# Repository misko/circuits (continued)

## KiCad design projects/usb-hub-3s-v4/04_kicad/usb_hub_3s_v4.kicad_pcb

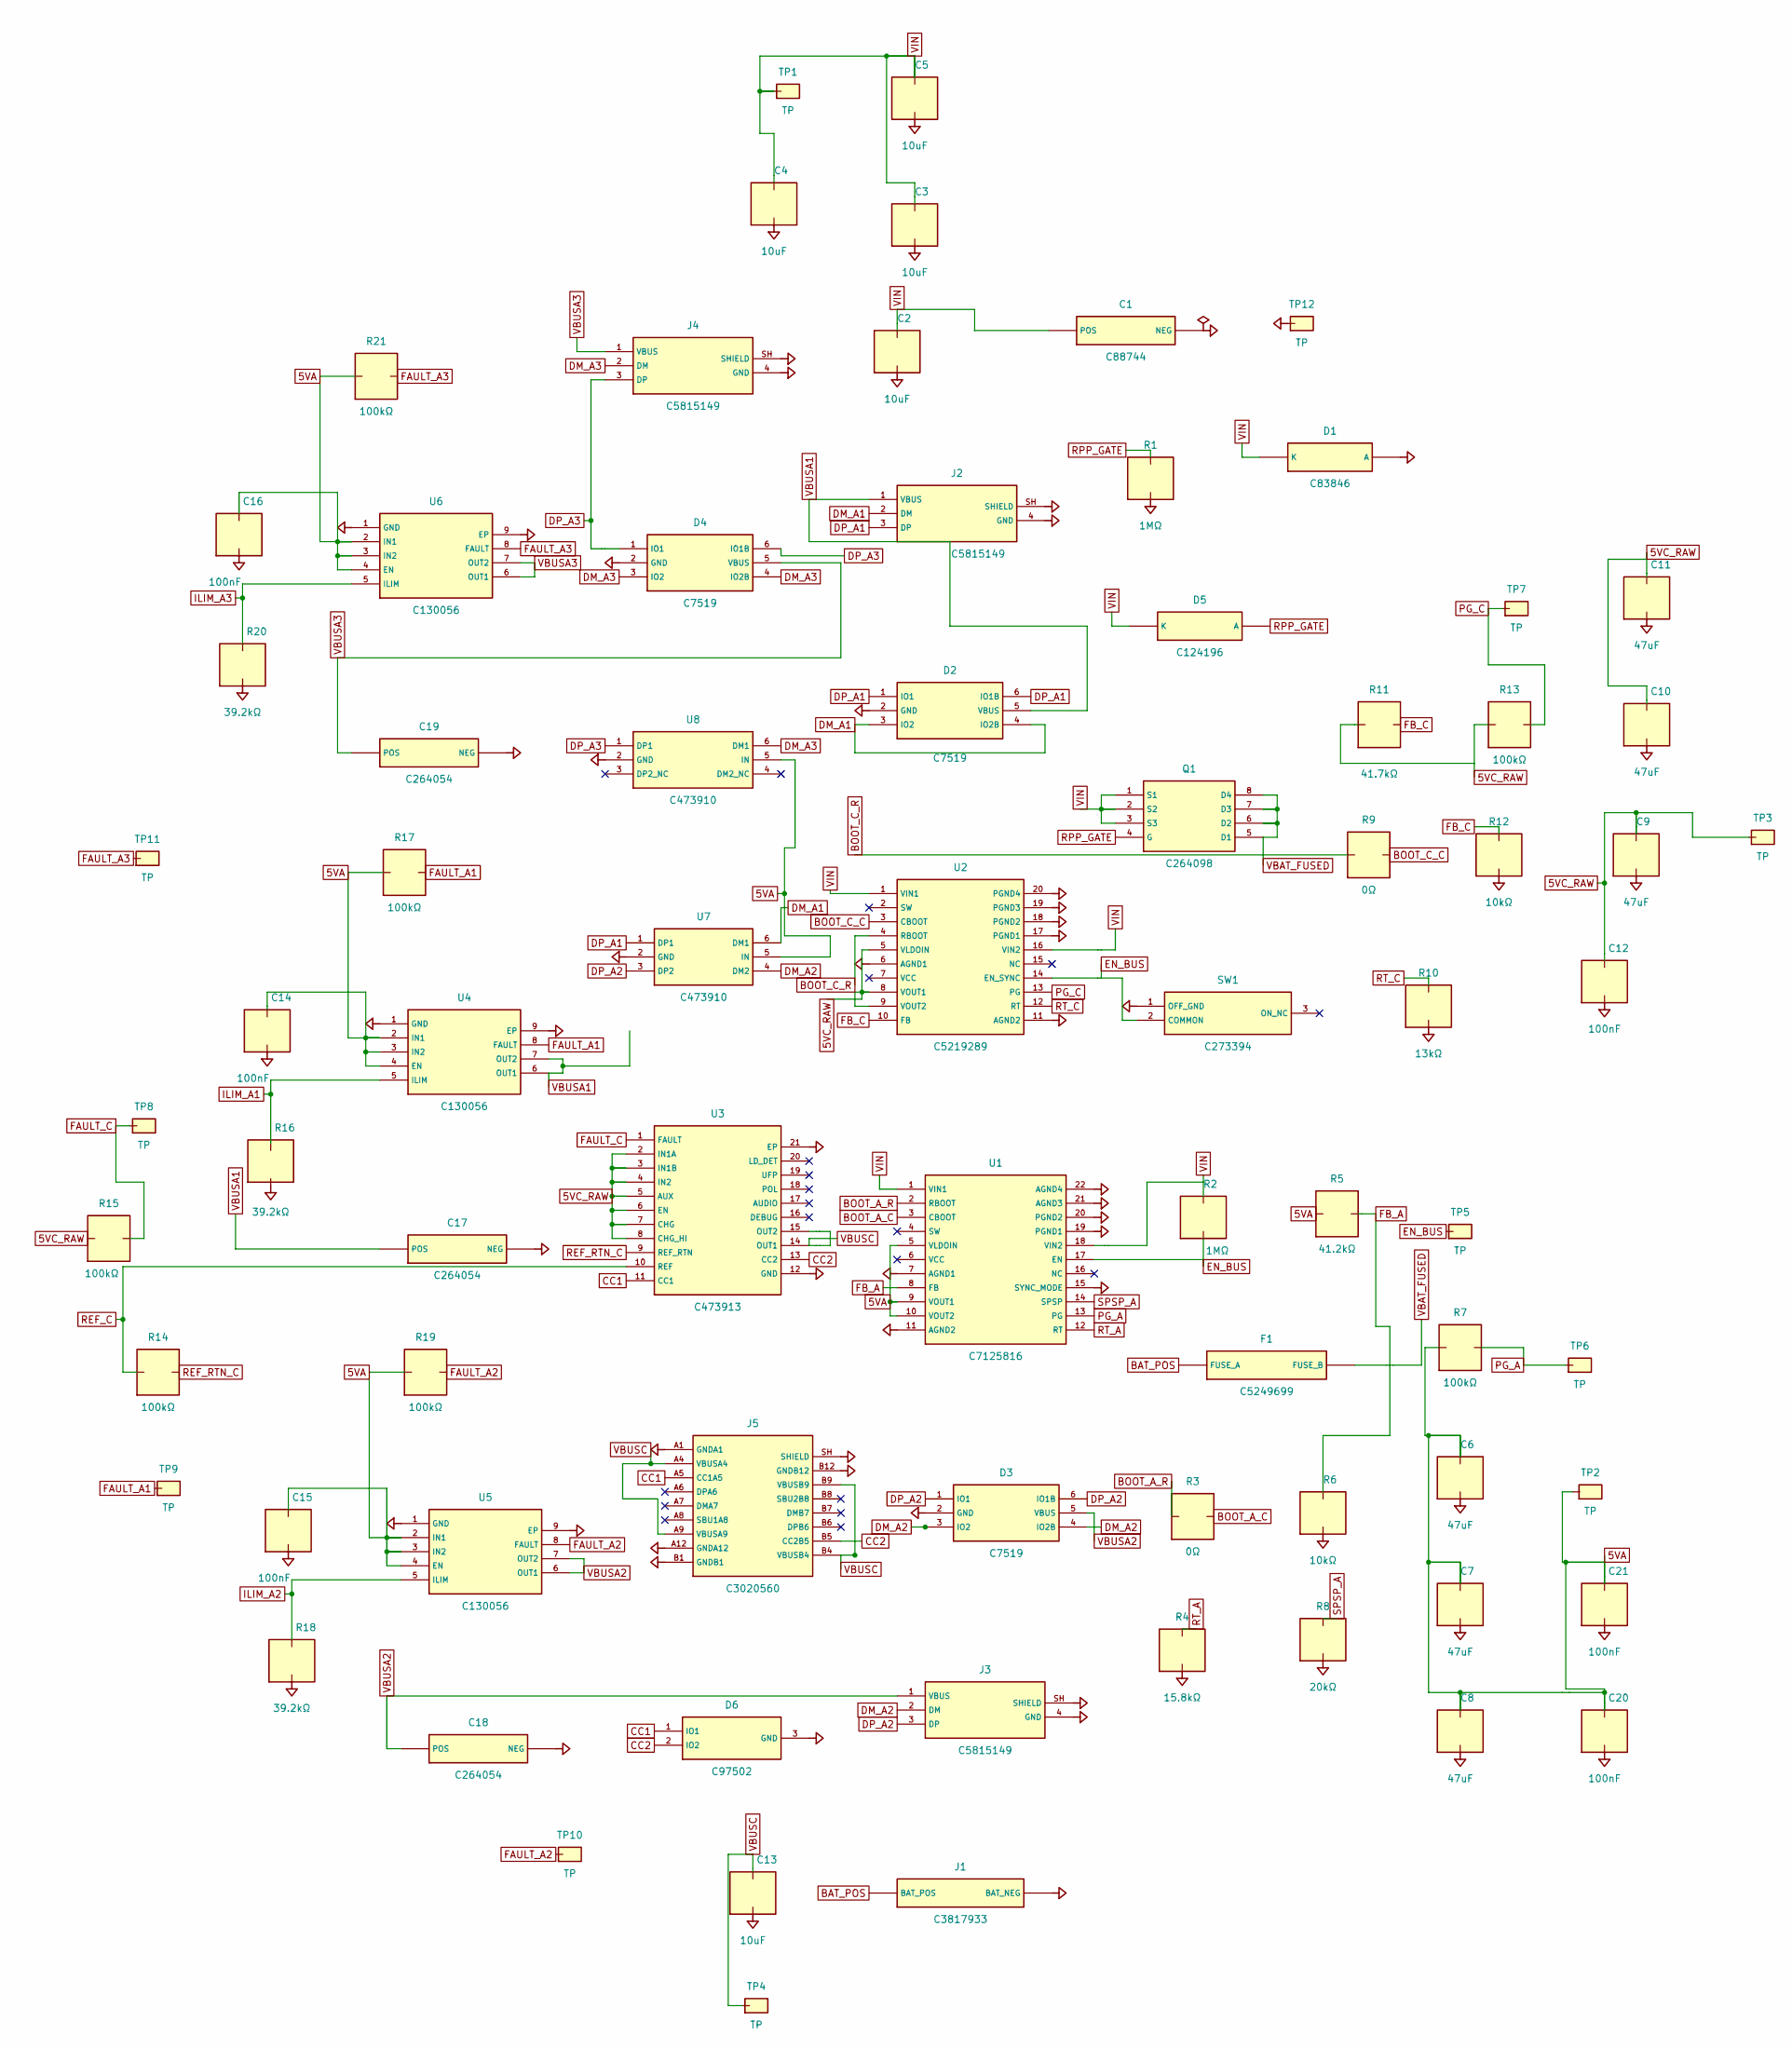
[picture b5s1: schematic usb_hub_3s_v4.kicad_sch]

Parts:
C1: C88744; Rubycon_TZV_D6.3x8
C2, C3, C4, C5, C13: 10uF; C_1210_3225Metric
C6, C7, C8, C9, C10, C11: 47uF; C_1210_3225Metric
C12, C14, C15, C16, C20, C21: 100nF; C_0402_1005Metric
C17, C18, C19: C264054; CP_Elec_6.3x5.8
D1: C83846; D_SMB
D2, D3, D4: C7519; SOT-23-6
D5: C124196; D_SOD-123
D6: C97502; SOT-9X3
F1: C5249699; Keystone_3568_Mini_Blade_Fuse_Holder
J1: C3817933; Phoenix_MKDS_1.5_2_1715022
J2, J3, J4: C5815149; USB_A_GCT_USB1130-15-A_Horizontal
J5: C3020560; GCT_USB4105_GF_A
Q1: C264098; Diodes_PowerDI3333-8_Type_UX
R1, R2: 1MΩ; R_0603_1608Metric
R3, R9: 0Ω; R_0603_1608Metric
R4: 15.8kΩ; R_0603_1608Metric
R5: 41.2kΩ; R_0603_1608Metric
R6, R12: 10kΩ; R_0603_1608Metric
R7, R13, R14, R15, R17, R19, R21: 100kΩ; R_0603_1608Metric
R8: 20kΩ; R_0603_1608Metric
R10: 13kΩ; R_0603_1608Metric
R11: 41.7kΩ; R_0603_1608Metric
R16, R18, R20: 39.2kΩ; R_0603_1608Metric
SW1: C273394; E_Switch_EG1218
TP1, TP2, TP3, TP4, TP5, TP6, TP7, TP8, TP9, TP10, TP11, TP12: TP; TestPoint_Pad_D1.5mm
U1: C7125816; Texas_RDF0022A_B3QFN-22_6.5x7.5mm_ThermalVias
U2: C5219289; Texas_RDL0020A_B3QFN-20_5x5.5mm_ThermalVias
U3: C473913; Texas_RVC0020A_WQFN-20-1EP_3x4mm_P0.5mm_EP1.6x2.6mm_Thermal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
U4, U5, U6: C130056; VSON-8-1EP_3x3mm_P0.65mm_EP1.65x2.4mm_ThermalVias
U7, U8: C473910; SOT-23-6

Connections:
5VA: C6.1, C7.1, C8.1, C14.1, C15.1, C16.1, C20.1, C21.1, R5.1, R7.1, R17.1, R19.1, R21.1, TP2.1, U1.5 (VLDOIN), U1.9 (VOUT1), U1.10 (VOUT2), U4.2 (IN1), U4.3 (IN2), U4.4 (EN), U5.2 (IN1), U5.3 (IN2), U5.4 (EN), U6.2 (IN1), U6.3 (IN2), U6.4 (EN), U7.5 (IN), U8.5 (IN)
5VC_RAW: C9.1, C10.1, C11.1, C12.1, R11.1, R13.1, R15.1, TP3.1, U2.5 (VLDOIN), U2.8 (VOUT1), U2.9 (VOUT2), U3.2 (IN1A), U3.3 (IN1B), U3.4 (IN2), U3.5 (AUX), U3.6 (EN), U3.7 (CHG), U3.8 (CHG_HI)
BAT_POS: F1.1 (FUSE_A), J1.1 (BAT_POS)
BOOT_A_C: R3.2, U1.3 (CBOOT)
BOOT_A_R: R3.1, U1.2 (RBOOT)
BOOT_C_C: R9.2, U2.3 (CBOOT)
BOOT_C_R: R9.1, U2.4 (RBOOT)
CC1: D6.1 (IO1), J5.A5 (CC1A5), U3.11 (CC1)
CC2: D6.2 (IO2), J5.B5 (CC2B5), U3.13 (CC2)
DM_A1: D2.3 (IO2), D2.4 (IO2B), J2.2 (DM), U7.6 (DM1)
DM_A2: D3.3 (IO2), D3.4 (IO2B), J3.2 (DM), U7.4 (DM2)
DM_A3: D4.3 (IO2), D4.4 (IO2B), J4.2 (DM), U8.6 (DM1)
DP_A1: D2.1 (IO1), D2.6 (IO1B), J2.3 (DP), U7.1 (DP1)
DP_A2: D3.1 (IO1), D3.6 (IO1B), J3.3 (DP), U7.3 (DP2)
DP_A3: D4.1 (IO1), D4.6 (IO1B), J4.3 (DP), U8.1 (DP1)
EN_BUS: R2.2, SW1.2 (COMMON), TP5.1, U1.17 (EN), U2.14 (EN_SYNC)
FAULT_A1: R17.2, TP9.1, U4.8 (FAULT)
FAULT_A2: R19.2, TP10.1, U5.8 (FAULT)
FAULT_A3: R21.2, TP11.1, U6.8 (FAULT)
FAULT_C: R15.2, TP8.1, U3.1 (FAULT)
FB_A: R5.2, R6.1, U1.8 (FB)
FB_C: R11.2, R12.1, U2.10 (FB)
GND: C1.2 (NEG), C2.2, C3.2, C4.2, C5.2, C6.2, C7.2, C8.2, C9.2, C10.2, C11.2, C12.2, C13.2, C14.2, C15.2, C16.2, C17.2 (NEG), C18.2 (NEG), C19.2 (NEG), C20.2, C21.2, D1.2 (A), D2.2 (GND), D3.2 (GND), D4.2 (GND), D6.3 (GND), J1.2 (BAT_NEG), J2.4 (GND), J2.SH (SHIELD), J3.4 (GND), J3.SH (SHIELD), J4.4 (GND), J4.SH (SHIELD), J5.A1 (GNDA1), J5.A12 (GNDA12), J5.B1 (GNDB1), J5.B12 (GNDB12), J5.SH (SHIELD), R1.2, R4.2, R6.2, R8.2, R10.2, R12.2, R16.2, R18.2, R20.2, SW1.1 (OFF_GND), TP12.1, U1.7 (AGND1), U1.11 (AGND2), U1.15 (SYNC_MODE), U1.19 (PGND1), U1.20 (PGND2), U1.21 (AGND3), U1.22 (AGND4), U2.6 (AGND1), U2.11 (AGND2), U2.17 (PGND1), U2.18 (PGND2), U2.19 (PGND3), U2.20 (PGND4), U3.12 (GND), U3.21 (EP), U4.1 (GND), U4.9 (EP), U5.1 (GND), U5.9 (EP), U6.1 (GND), U6.9 (EP), U7.2 (GND), U8.2 (GND)
ILIM_A1: R16.1, U4.5 (ILIM)
ILIM_A2: R18.1, U5.5 (ILIM)
ILIM_A3: R20.1, U6.5 (ILIM)
PG_A: R7.2, TP6.1, U1.13 (PG)
PG_C: R13.2, TP7.1, U2.13 (PG)
REF_C: R14.1, U3.10 (REF)
REF_RTN_C: R14.2, U3.9 (REF_RTN)
RPP_GATE: D5.2 (A), Q1.4 (G), R1.1
RT_A: R4.1, U1.12 (RT)
RT_C: R10.1, U2.12 (RT)
SPSP_A: R8.1, U1.14 (SPSP)
VBAT_FUSED: F1.2 (FUSE_B), Q1.5 (D1), Q1.6 (D2), Q1.7 (D3), Q1.8 (D4)
VBUSA1: C17.1 (POS), D2.5 (VBUS), J2.1 (VBUS), U4.6 (OUT1), U4.7 (OUT2)
VBUSA2: C18.1 (POS), D3.5 (VBUS), J3.1 (VBUS), U5.6 (OUT1), U5.7 (OUT2)
VBUSA3: C19.1 (POS), D4.5 (VBUS), J4.1 (VBUS), U6.6 (OUT1), U6.7 (OUT2)
VBUSC: C13.1, J5.A4 (VBUSA4), J5.A9 (VBUSA9), J5.B4 (VBUSB4), J5.B9 (VBUSB9), TP4.1, U3.14 (OUT1), U3.15 (OUT2)
VIN: C1.1 (POS), C2.1, C3.1, C4.1, C5.1, D1.1 (K), D5.1 (K), Q1.1 (S1), Q1.2 (S2), Q1.3 (S3), R2.1, TP1.1, U1.1 (VIN1), U1.18 (VIN2), U2.1 (VIN1), U2.16 (VIN2)

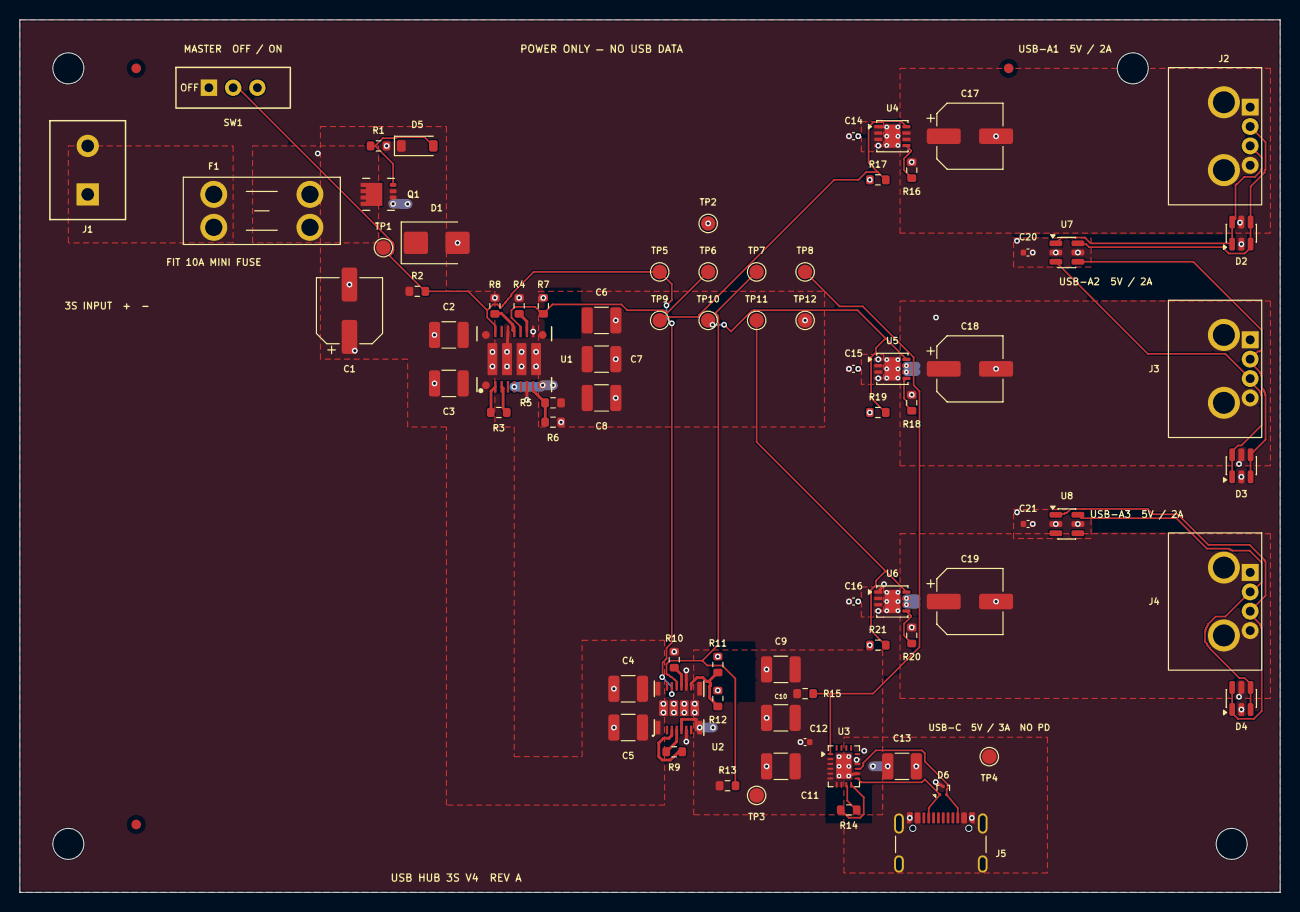
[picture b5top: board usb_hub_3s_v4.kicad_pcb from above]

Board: 4 copper layers, 130.0 x 90.0 mm, 83 parts (0 on the bottom side), 40 nets.

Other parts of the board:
FID1, FID2, FID3: Fiducial_1mm_Mask2mm
H1, H2, H3, H4: MountingHole_3.2mm_M3
